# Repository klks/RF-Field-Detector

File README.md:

# RFID Field Detector Card

I wanted a quick way to tell what kind of RFID field a reader is putting out
without plugging anything in, so I made this. It's a credit-card-sized PCB with
three antennas on it. Hold it near a reader and an LED lights up:

- amber for 125 kHz (EM4100, HID Prox, T5577 etc.)
- green for 13.56 MHz (NFC, MIFARE, iCLASS)
- red for UHF 860-960 MHz

There's no battery. The reader's field powers the LED.

## What's in here

The KiCad 10 project is in `PCB/` (open `RFID_FieldDetector.kicad_pro`). The
custom coil and antenna footprints are in `PCB/RFID_Detector.pretty/`, and
there's a PDF of the schematic if you just want to look at it.

`PCB/production/` has the gerber zip, BOM and pick-and-place files, ready to
upload to JLCPCB or whoever you use.

## Getting it made

Order it as 2-layer FR4, **1.0 mm thick, 1 oz copper**. The board thickness
matters because the coil tuning was worked out for 1.0 mm. If you go with
1.6 mm you'll need to retune (C2 ended up around 2.7 nF and C5 around 22 pF
at that thickness). Colour and finish don't matter. Nothing on it is
fine-pitch enough to need anything special from the fab.

## Parts

Everything goes on the top side. It's all 0805 except D3.

| Ref | Value | Notes |
|---|---|---|
| C1 | 15 nF | |
| C2 | 2.2 nF | LF tuning |
| C3 | not fitted | extra LF tuning pad |
| C4 | 150 pF | |
| C5 | 10 pF | HF tuning |
| C6 | not fitted | extra HF tuning pad |
| C7 | 22 pF | |
| C8 | 100 pF | |
| R1-R3 | 47R | |
| D1 | amber LED | |
| D2 | green LED | |
| D3 | 1SS351-TB-E | Schottky pair, SC-59. BAT15-04R also works but check the pinout |
| D4 | red LED | |

Recommended to use C0G/NP0 caps for all of them.

## How it works

The LF and HF sides are just a coil and capacitor tuned to the carrier
frequency, with the LED across them. The LED rectifies the voltage the reader
induces, and that's enough to light it.

UHF is a bit different. The zig-zag trace around the edge is a dipole antenna,
and it feeds a small voltage doubler (C7, D3, C8) that drives the red LED.

The three circuits aren't connected, so each one only reacts to its own band.

Range depends a lot on the reader. 125 kHz needs to be pretty much touching,
13.56 MHz works from a couple of cm, and UHF lights from about 25-40 cm on a
4 W fixed reader, less on a handheld.

## Tuning

The values are calculated so yours might need a tweak:

- **Green weak?** Try different values for C5 (somewhere between 4.7 and
  27 pF), or put something on C6.
- **Amber weak?** Same thing with C2/C3, try 1 to 4.7 nF.
- **Red weak?** I made the antenna a bit long on purpose, because cutting it
  shorter is easy but making it longer isn't. Trim a couple of mm off the far
  end of both arms with a knife, keep them the same length, and test again.
  Stop when it stops getting better. If you're on the EU 866 MHz band, leave
  it alone.
- **LED too bright up close?** Bump R1-R3 to 100R.

## License

MIT

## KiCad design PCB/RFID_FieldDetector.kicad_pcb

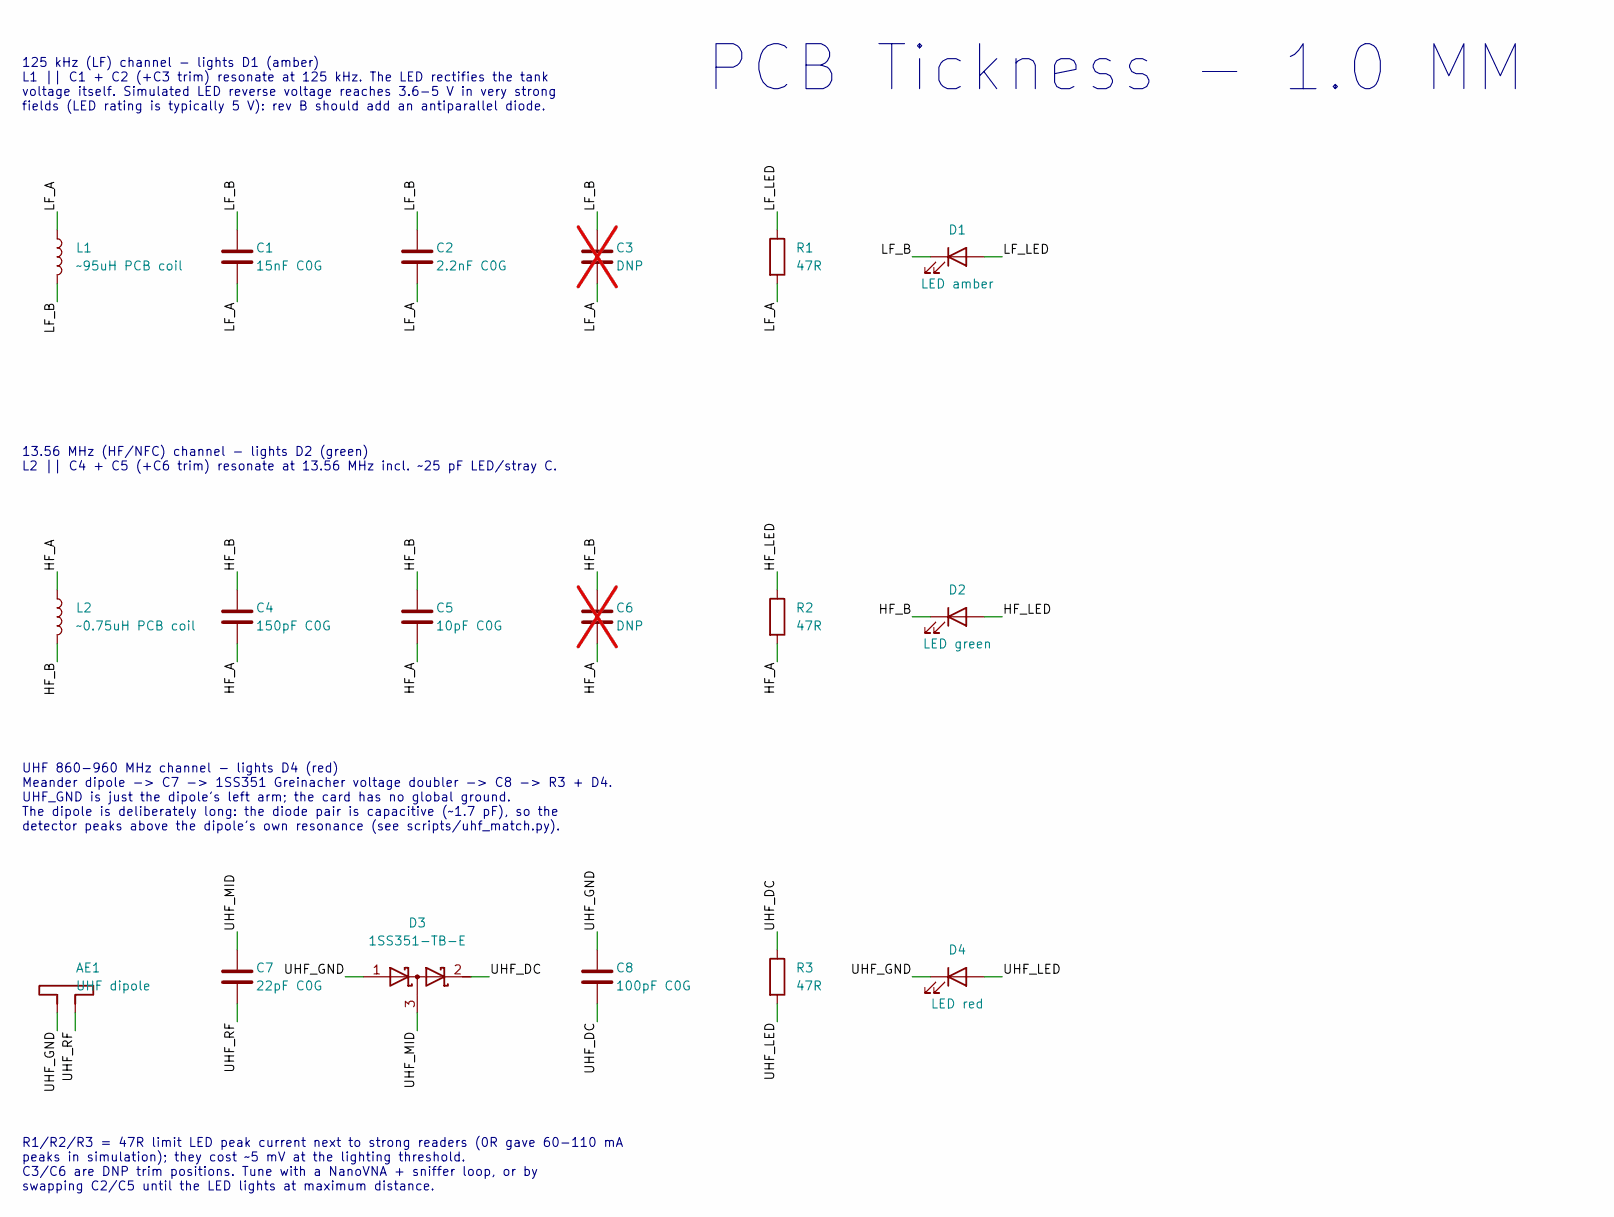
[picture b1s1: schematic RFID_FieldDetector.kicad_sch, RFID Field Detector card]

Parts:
AE1: UHF dipole; Antenna_UHF_Meander
C1: 15nF C0G; C_0805_2012Metric_Pad1.18x1.45mm_HandSolder
C2: 2.2nF C0G; C_0805_2012Metric_Pad1.18x1.45mm_HandSolder
C3, C6: DNP; C_0805_2012Metric_Pad1.18x1.45mm_HandSolder; not fitted
C4: 150pF C0G; C_0805_2012Metric_Pad1.18x1.45mm_HandSolder
C5: 10pF C0G; C_0805_2012Metric_Pad1.18x1.45mm_HandSolder
C7: 22pF C0G; C_0805_2012Metric_Pad1.18x1.45mm_HandSolder
C8: 100pF C0G; C_0805_2012Metric_Pad1.18x1.45mm_HandSolder
D1: LED amber; LED_0805_2012Metric_Pad1.15x1.40mm_HandSolder; MPN Kingbright APT2012SECK (orange 601 nm, 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
D2: LED green; LED_0805_2012Metric_Pad1.15x1.40mm_HandSolder; MPN Kingbright APT2012SGC (green 568 nm, Vf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
D3: 1SS351-TB-E; SC-59_Handsoldering; MPN onsemi 1SS351-TB-E (SC-59)
D4: LED red; LED_0805_2012Metric_Pad1.15x1.40mm_HandSolder; MPN Kingbright APT2012SURCK (hyper red 630 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
L1: ~95uH PCB coil; Coil_LF
L2: ~0.75uH PCB coil; Coil_HF
R1, R2, R3: 47R; R_0805_2012Metric_Pad1.20x1.40mm_HandSolder

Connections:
/HF_A: C4.2, C5.2, C6.2, L2.1, R2.2
/HF_B: C4.1, C5.1, C6.1, D2.1 (K), L2.2
/HF_LED: D2.2 (A), R2.1
/LF_A: C1.2, C2.2, C3.2, L1.1, R1.2
/LF_B: C1.1, C2.1, C3.1, D1.1 (K), L1.2
/LF_LED: D1.2 (A), R1.1
/UHF_DC: C8.2, D3.2 (K), R3.1
/UHF_GND: AE1.1, C8.1, D3.1 (A), D4.1 (K)
/UHF_LED: D4.2 (A), R3.2
/UHF_MID: C7.1, D3.3 (common)
/UHF_RF: AE1.2, C7.2

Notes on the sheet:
PCB Tickness - 1.0 MM
R1/R2/R3 = 47R limit LED peak current next to strong readers (0R gave 60-110 mA peaks in simulation); they cost ~5 mV at the lighting threshold. C3/C6 are DNP trim positions. Tune with a NanoVNA + sniffer loop, or by swapping C2/C5 until the LED lights at maximum distance.
UHF 860-960 MHz channel - lights D4 (red) Meander dipole -> C7 -> 1SS351 Greinacher voltage doubler -> C8 -> R3 + D4. UHF_GND is just the dipole's left arm; the card has no global ground. The dipole is deliberately long: the diode pair is capacitive (~1.7 pF), so the detector peaks above the dipole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
125 kHz (LF) channel - lights D1 (amber) L1 || C1 + C2 (+C3 trim) resonate at 125 kHz. The LED rectifies the tank voltage itself. Simulated LED reverse voltage reaches 3.6-5 V in very strong fields (LED rating is typically 5 V): rev B should add an antiparallel diode.
13.56 MHz (HF/NFC) channel - lights D2 (green) L2 || C4 + C5 (+C6 trim) resonate at 13.56 MHz incl. ~25 pF LED/stray C.

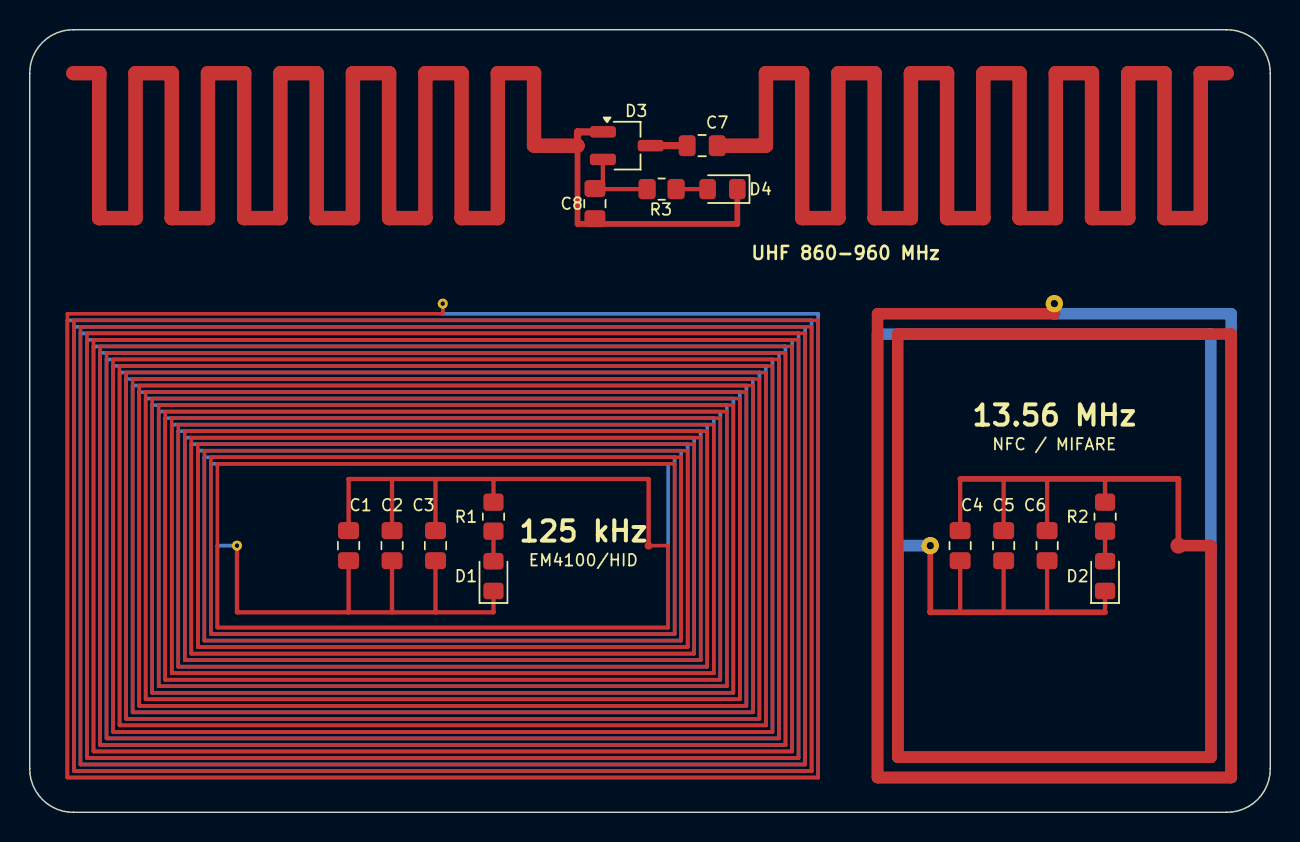
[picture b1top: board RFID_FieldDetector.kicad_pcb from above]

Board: 2 copper layers, 85.6 x 54.0 mm, 19 parts (1 on the bottom side), 11 nets.

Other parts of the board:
LOGO1: logo

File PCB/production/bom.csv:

Designator,Footprint,Quantity,Value,LCSC Part #
C1,0805,1,15nF C0G,
C2,0805,1,2.2nF C0G,
C4,0805,1,150pF C0G,
C5,0805,1,10pF C0G,
C7,0805,1,22pF C0G,
C8,0805,1,100pF C0G,
D1,0805,1,LED amber,"Kingbright APT2012SECK (orange 601 nm, Vf~2.0 V)"
D2,0805,1,LED green,"Kingbright APT2012SGC (green 568 nm, Vf~2.2 V)"
D3,SC-59_Handsoldering,1,1SS351-TB-E,onsemi 1SS351-TB-E (SC-59)
D4,0805,1,LED red,"Kingbright APT2012SURCK (hyper red 630 nm, Vf~1.95 V)"
"R1, R2, R3",0805,3,47R,
